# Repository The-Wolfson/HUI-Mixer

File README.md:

# HUI Mixer
A versatile HUI device for mixing in any DAW that supports peripherals (Logic Pro, Pro Tools, CuBase).

Schematic:

PCB:

Assembled:

## BOM
| Part | Quantity |
| --- | --- |
| EC11 Rotary Encoder | 2 |
| MX-Style Switch | 6 |
| SK6812 MINI-E LED | 16 |
| M3x16mm Screw | 4 |

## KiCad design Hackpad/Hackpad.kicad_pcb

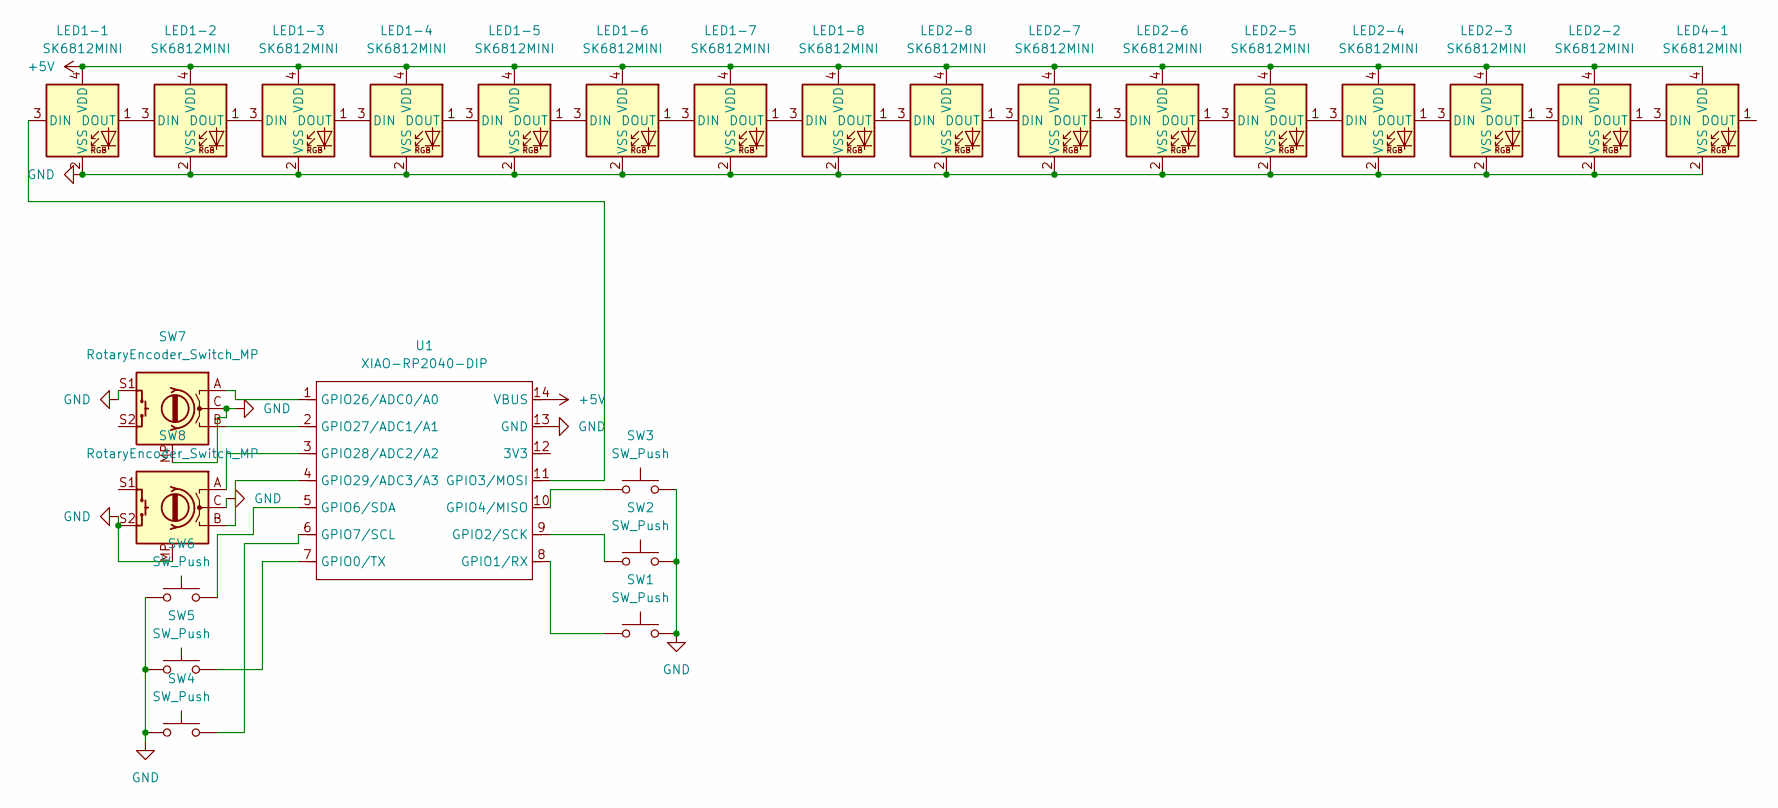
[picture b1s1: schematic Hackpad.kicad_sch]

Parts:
LED1-1, LED1-2, LED1-3, LED1-4, LED1-5, LED1-6, LED1-7, LED1-8, LED2-2, LED2-3, LED2-4, LED2-5, LED2-6, LED2-7, LED2-8, LED4-1: SK6812MINI; LED_SK6812MINI_PLCC4_3.5x3.5mm_P1.75mm
SW1, SW2, SW3, SW4, SW5, SW6: SW_Push; SW_Cherry_MX_1.00u_PCB
SW7, SW8: RotaryEncoder_Switch_MP; RotaryEncoder_Alps_EC11E-Switch_Vertical_H20mm
U1: XIAO-RP2040-DIP

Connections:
+5V: LED1-1.4 (VDD), LED1-2.4 (VDD), LED1-3.4 (VDD), LED1-4.4 (VDD), LED1-5.4 (VDD), LED1-6.4 (VDD), LED1-7.4 (VDD), LED1-8.4 (VDD), LED2-2.4 (VDD), LED2-3.4 (VDD), LED2-4.4 (VDD), LED2-5.4 (VDD), LED2-6.4 (VDD), LED2-7.4 (VDD), LED2-8.4 (VDD), LED4-1.4 (VDD), U1.14 (VBUS)
GND: LED1-1.2 (VSS), LED1-2.2 (VSS), LED1-3.2 (VSS), LED1-4.2 (VSS), LED1-5.2 (VSS), LED1-6.2 (VSS), LED1-7.2 (VSS), LED1-8.2 (VSS), LED2-2.2 (VSS), LED2-3.2 (VSS), LED2-4.2 (VSS), LED2-5.2 (VSS), LED2-6.2 (VSS), LED2-7.2 (VSS), LED2-8.2 (VSS), LED4-1.2 (VSS), SW1.2, SW2.2, SW3.2, SW4.2, SW5.2, SW6.2, SW7.C, SW7.MP, SW7.S1, SW8.C, SW8.MP, SW8.S2, U1.13 (GND)
unnamed: LED1-1.3 (DIN), U1.11 (GPIO3/MOSI)
unnamed: LED1-1.1 (DOUT), LED1-2.3 (DIN)
unnamed: LED1-2.1 (DOUT), LED1-3.3 (DIN)
unnamed: LED1-3.1 (DOUT), LED1-4.3 (DIN)
unnamed: LED1-4.1 (DOUT), LED1-5.3 (DIN)
unnamed: LED1-5.1 (DOUT), LED1-6.3 (DIN)
unnamed: LED1-6.1 (DOUT), LED1-7.3 (DIN)
unnamed: LED1-7.1 (DOUT), LED1-8.3 (DIN)
unnamed: LED1-8.1 (DOUT), LED2-8.3 (DIN)
unnamed: LED2-2.3 (DIN), LED2-3.1 (DOUT)
unnamed: LED2-2.1 (DOUT), LED4-1.3 (DIN)
unnamed: LED2-3.3 (DIN), LED2-4.1 (DOUT)
unnamed: LED2-4.3 (DIN), LED2-5.1 (DOUT)
unnamed: LED2-5.3 (DIN), LED2-6.1 (DOUT)
unnamed: LED2-6.3 (DIN), LED2-7.1 (DOUT)
unnamed: LED2-7.3 (DIN), LED2-8.1 (DOUT)
unnamed: SW5.1, U1.7 (GPIO0/TX)
unnamed: SW1.1, U1.8 (GPIO1/RX)
unnamed: SW2.1, U1.9 (GPIO2/SCK)
unnamed: SW3.1, U1.10 (GPIO4/MISO)
unnamed: SW6.1, U1.5 (GPIO6/SDA)
unnamed: SW4.1, U1.6 (GPIO7/SCL)
unnamed: SW7.A, U1.1 (GPIO26/ADC0/A0)
unnamed: SW7.B, U1.2 (GPIO27/ADC1/A1)
unnamed: SW8.A, U1.3 (GPIO28/ADC2/A2)
unnamed: SW8.B, U1.4 (GPIO29/ADC3/A3)

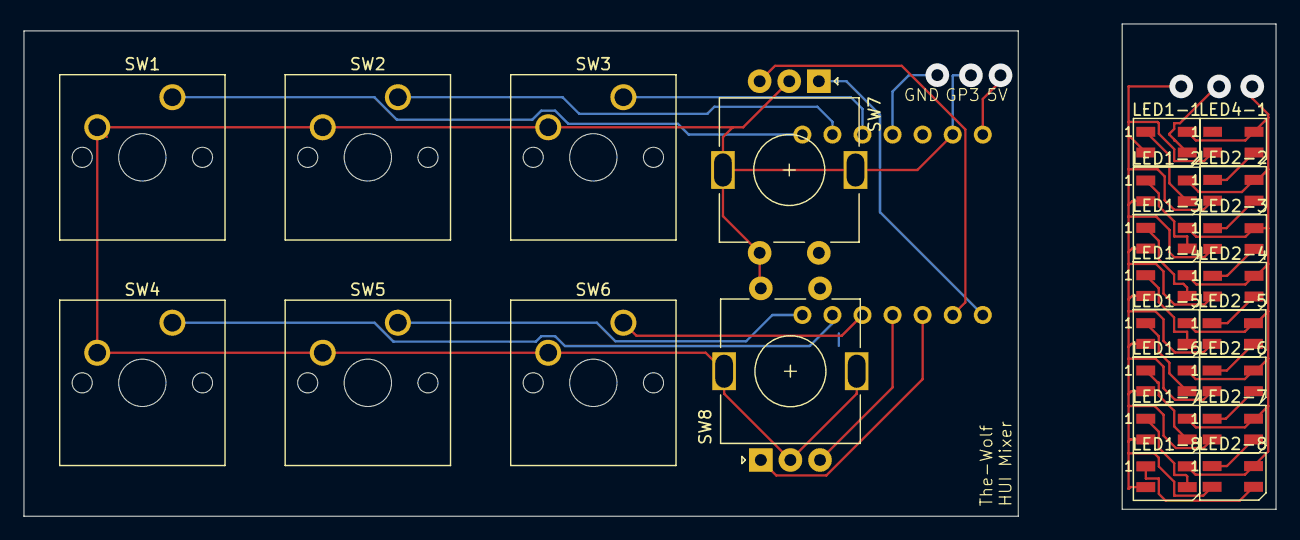
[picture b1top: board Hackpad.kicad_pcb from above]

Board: 2 copper layers, 105.8 x 41.6 mm, 25 parts (1 on the bottom side), 28 nets.
